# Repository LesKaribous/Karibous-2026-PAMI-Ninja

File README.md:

# Karibous-2026-PAMI-Ninja
PAMI Ninja - Coupe de France de robotique 2026

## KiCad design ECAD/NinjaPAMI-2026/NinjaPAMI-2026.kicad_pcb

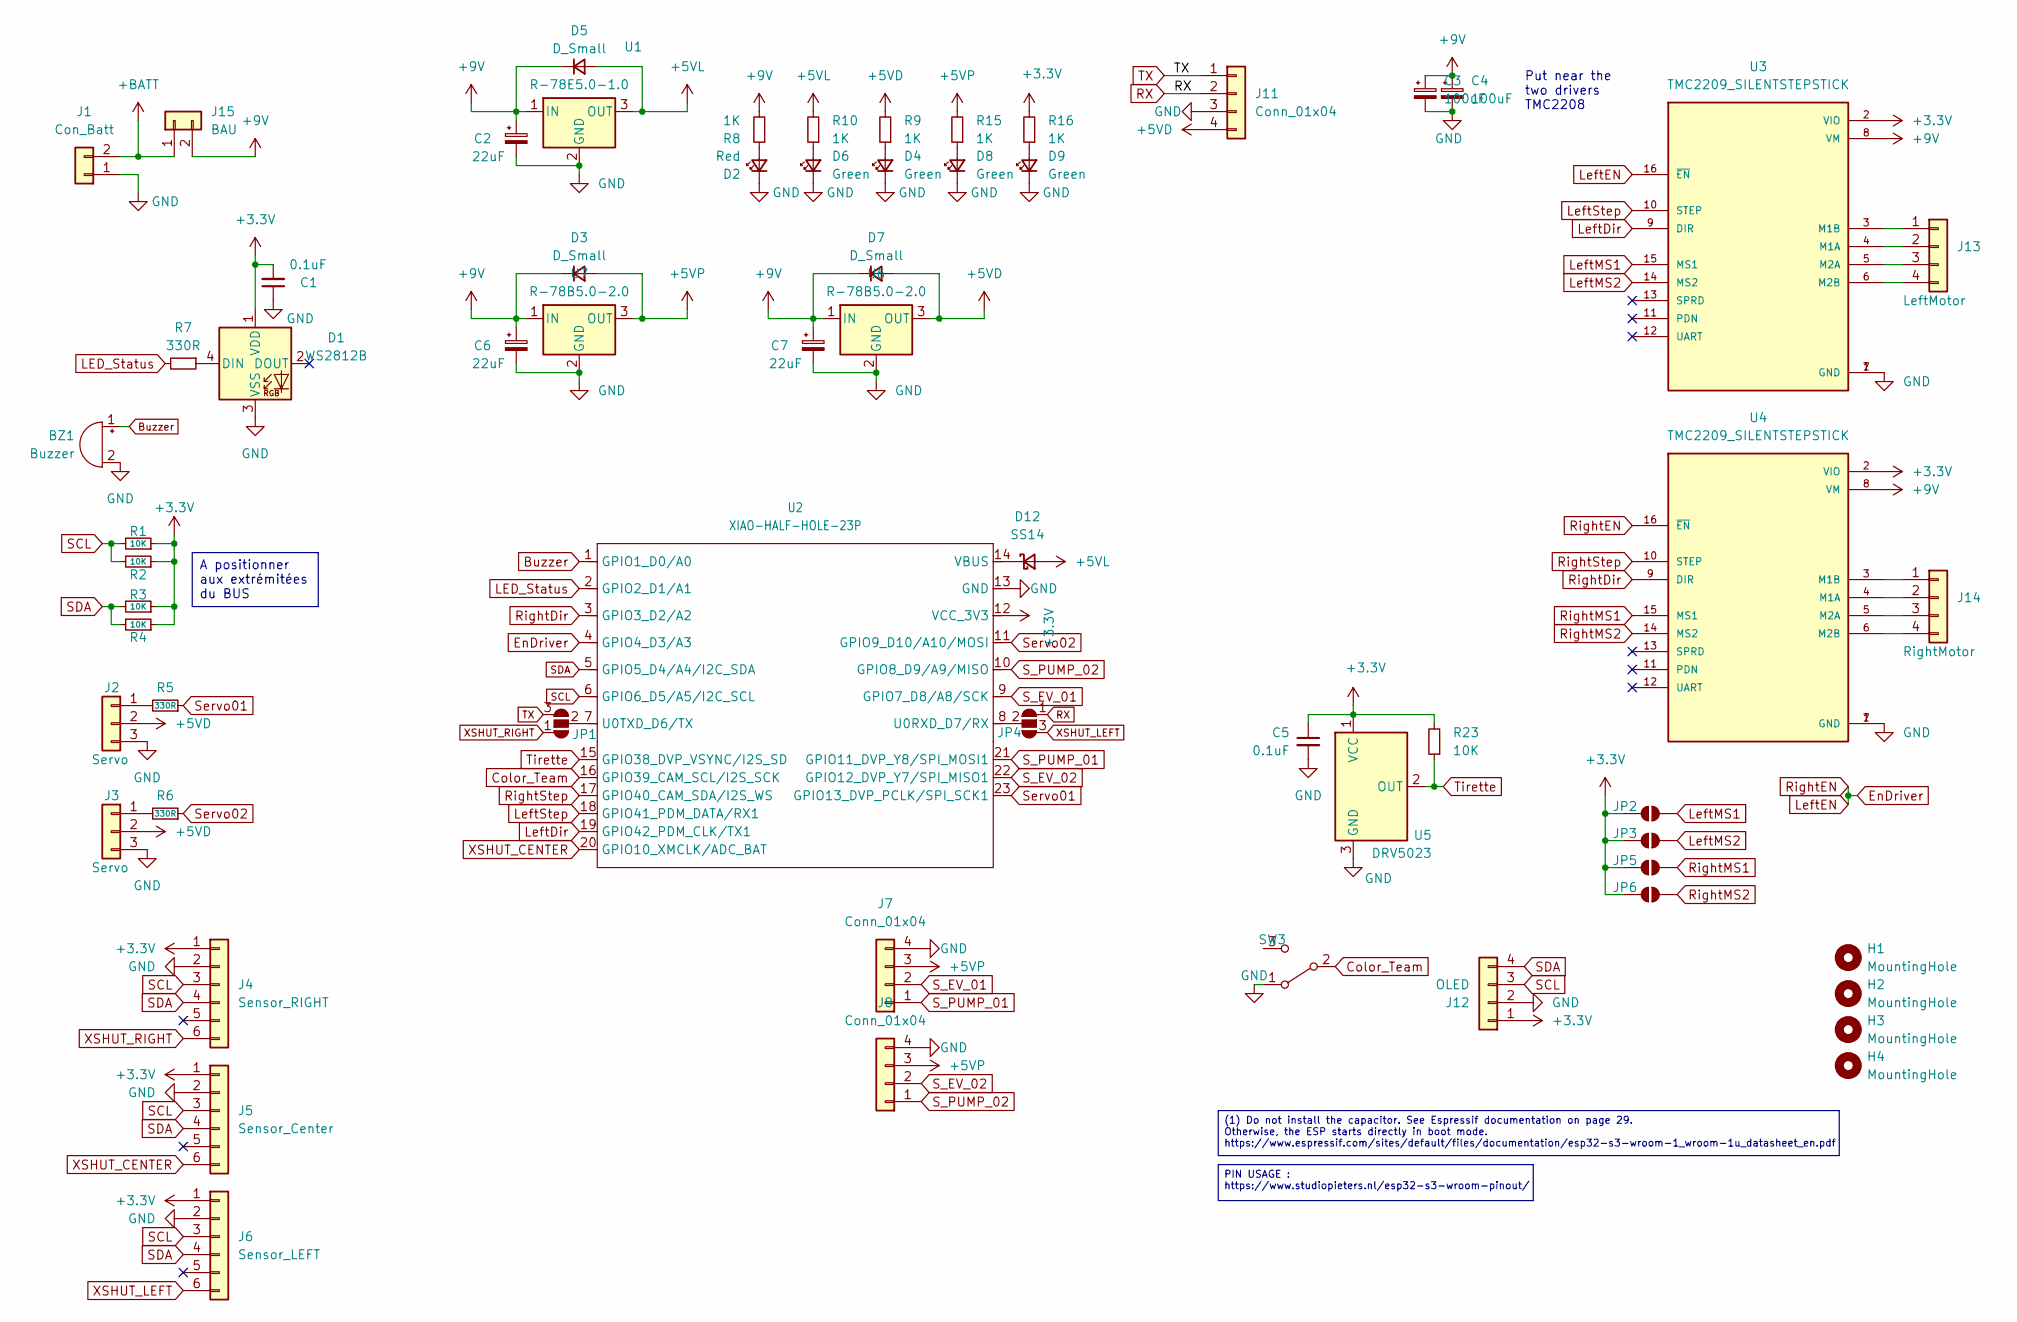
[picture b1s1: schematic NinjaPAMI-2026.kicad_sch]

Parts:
BZ1: Buzzer; Buzzer_12x9.5RM7.6
C1: 0.1uF; C_1206_3216Metric
C2, C6, C7: 22uF; CP_Elec_5x5.4
C3, C4: 100uF; CP_Radial_D8.0mm_P3.50mm
C5: 0.1uF; C_1206_3216Metric_Pad1.33x1.80mm_HandSolder
D1: WS2812B; LED_WS2812B_PLCC4_5.0x5.0mm_P3.2mm
D2: Red; LED_1206_3216Metric
D3, D5, D7: D_Small; D_SMA_Handsoldering
D4, D6, D8, D9: Green; LED_1206_3216Metric
D12: SS14; D_SMA_Handsoldering
H1, H2, H3, H4: MountingHole; MountingHole_3.2mm_M3
J1: Con_Batt; Molex_KK-254_AE-6410-02A_1x02_P2.54mm_Vertical
J2, J3: Servo; PinHeader_1x03_P2.54mm_Vertical
J4: Sensor_RIGHT; Molex_KK-254_AE-6410-06A_1x06_P2.54mm_Vertical
J5: Sensor_Center; Molex_KK-254_AE-6410-06A_1x06_P2.54mm_Vertical
J6: Sensor_LEFT; Molex_KK-254_AE-6410-06A_1x06_P2.54mm_Vertical
J7, J8, J11: Conn_01x04; Molex_KK-254_AE-6410-04A_1x04_P2.54mm_Vertical
J12: OLED; Molex_KK-254_AE-6410-04A_1x04_P2.54mm_Vertical
J13: LeftMotor; Molex_KK-254_AE-6410-04A_1x04_P2.54mm_Vertical
J14: RightMotor; Molex_KK-254_AE-6410-04A_1x04_P2.54mm_Vertical
J15: BAU; Molex_KK-254_AE-6410-02A_1x02_P2.54mm_Vertical
JP1, JP4: SolderJumper_3_Open; SolderJumper-3_P1.3mm_Open_RoundedPad1.0x1.5mm_NumberLabels
JP2, JP3, JP5, JP6: SolderJumper_2_Open; SolderJumper-2_P1.3mm_Open_RoundedPad1.0x1.5mm
R1, R2, R3, R4, R23: 10K; R_1206_3216Metric_Pad1.30x1.75mm_HandSolder
R5, R6, R7: 330R; R_1206_3216Metric_Pad1.30x1.75mm_HandSolder
R8, R9, R10, R15, R16: 1K; R_1206_3216Metric_Pad1.30x1.75mm_HandSolder
SW3: SW_SPDT; SK-12D10 1P2T
U1: R-78E5.0-1.0; Converter_DCDC_RECOM_R-78E-0.5_THT
U2: XIAO-HALF-HOLE-23P; MOUDLE23P-SMD-2.54-21X17.8MM.kicad_mod.kicad_sym
U3, U4: TMC2209_SILENTSTEPSTICK; MODULE_TMC2209_SILENTSTEPSTICK; PARTREV 1.20
U5: DRV5023; SOT-23_Handsoldering
U6, U7: R-78B5.0-2.0; Converter_DCDC_RECOM_R-78B-2.0_THT

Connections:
+3.3V: C1.2, C5.1, D1.1 (VDD), J4.1, J5.1, J6.1, J12.1, JP2.1 (A), JP3.1 (A), JP5.1 (A), JP6.1 (A), R1.1, R2.1, R3.1, R4.1, R16.2, R23.2, U2.12 (VCC_3V3), U3.2 (VIO), U4.2 (VIO), U5.1 (VCC)
+5VD: D7.2 (A), J2.2, J3.2, J11.4, R9.2, U6.3 (OUT)
+5VL: D5.2 (A), D12.2 (A), R10.2, U1.3 (OUT)
+5VP: D3.2 (A), J7.3, J8.3, R15.2, U7.3 (OUT)
+9V: C2.1, C3.1, C4.1, C6.1, C7.1, D3.1 (K), D5.1 (K), D7.1 (K), J15.2, R8.2, U1.1 (IN), U3.8 (VM), U4.8 (VM), U6.1 (IN), U7.1 (IN)
+BATT: J1.2, J15.1
Buzzer: BZ1.1 (+), U2.1 (GPIO1_D0/A0)
Color_Team: SW3.2 (B), U2.16 (GPIO39_CAM_SCL/I2S_SCK)
EnDriver: U2.4 (GPIO4_D3/A3), U3.16 (~EN), U4.16 (~EN)
GND: BZ1.2 (-), C1.1, C2.2, C3.2, C4.2, C5.2, C6.2, C7.2, D1.3 (VSS), D2.1 (K), D4.1 (K), D6.1 (K), D8.1 (K), D9.1 (K), J1.1, J2.3, J3.3, J4.2, J5.2, J6.2, J7.4, J8.4, J11.3, J12.2, SW3.1 (A), U1.2 (GND), U2.13 (GND), U3.1 (GND), U3.7 (GND), U4.1 (GND), U4.7 (GND), U5.3 (GND), U6.2 (GND), U7.2 (GND)
LED_Status: R7.2, U2.2 (GPIO2_D1/A1)
LeftDir: U2.19 (GPIO42_PDM_CLK/TX1), U3.9 (DIR)
LeftMS1: JP2.2 (B), U3.15 (MS1)
LeftMS2: JP3.2 (B), U3.14 (MS2)
LeftStep: U2.18 (GPIO41_PDM_DATA/RX1), U3.10 (STEP)
unnamed: D1.4 (DIN), R7.1
unnamed: D2.2 (A), R8.1
unnamed: D4.2 (A), R9.1
unnamed: D6.2 (A), R10.1
unnamed: D8.2 (A), R15.1
unnamed: D9.2 (A), R16.1
unnamed: D12.1 (K), U2.14 (VBUS)
unnamed: J2.1, R5.2
unnamed: J3.1, R6.2
unnamed: J13.1, U3.3 (M1B)
unnamed: J13.2, U3.4 (M1A)
unnamed: J13.3, U3.5 (M2A)
unnamed: J13.4, U3.6 (M2B)
unnamed: J14.1, U4.3 (M1B)
unnamed: J14.2, U4.4 (M1A)
unnamed: J14.3, U4.5 (M2A)
unnamed: J14.4, U4.6 (M2B)
unnamed: JP1.2 (C), U2.7 (U0TXD_D6/TX)
unnamed: JP4.2 (C), U2.8 (U0RXD_D7/RX)
RX: J11.2, JP4.1 (A)
RightDir: U2.3 (GPIO3_D2/A2), U4.9 (DIR)
RightMS1: JP5.2 (B), U4.15 (MS1)
RightMS2: JP6.2 (B), U4.14 (MS2)
RightStep: U2.17 (GPIO40_CAM_SDA/I2S_WS), U4.10 (STEP)
SCL: J4.3, J5.3, J6.3, J12.3, R1.2, R2.2, U2.6 (GPIO6_D5/A5/I2C_SCL)
SDA: J4.4, J5.4, J6.4, J12.4, R3.2, R4.2, U2.5 (GPIO5_D4/A4/I2C_SDA)
S_EV_01: J7.2, U2.9 (GPIO7_D8/A8/SCK)
S_EV_02: J8.2, U2.22 (GPIO12_DVP_Y7/SPI_MISO1)
S_PUMP_01: J7.1, U2.21 (GPIO11_DVP_Y8/SPI_MOSI1)
S_PUMP_02: J8.1, U2.10 (GPIO8_D9/A9/MISO)
Servo01: R5.1, U2.23 (GPIO13_DVP_PCLK/SPI_SCK1)
Servo02: R6.1, U2.11 (GPIO9_D10/A10/MOSI)
TX: J11.1, JP1.3 (B)
Tirette: R23.1, U2.15 (GPIO38_DVP_VSYNC/I2S_SD), U5.2 (OUT)
XSHUT_CENTER: J5.6, U2.20 (GPIO10_XMCLK/ADC_BAT)
XSHUT_LEFT: J6.6, JP4.3 (B)
XSHUT_RIGHT: J4.6, JP1.1 (A)

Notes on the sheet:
Put near the two drivers TMC2208
PIN USAGE : https://www.studiopieters.nl/esp32-s3-wroom-pinout/
A positionner aux extrémitées du BUS
(1) Do not install the capacitor. See Espressif documentation on page 29. Otherwise, the ESP starts directly in boot mode. https://www.espressif.com/sites/default/files/documentation/esp32-s3-wroom-1_wroom-1u_datasheet_en.pdf

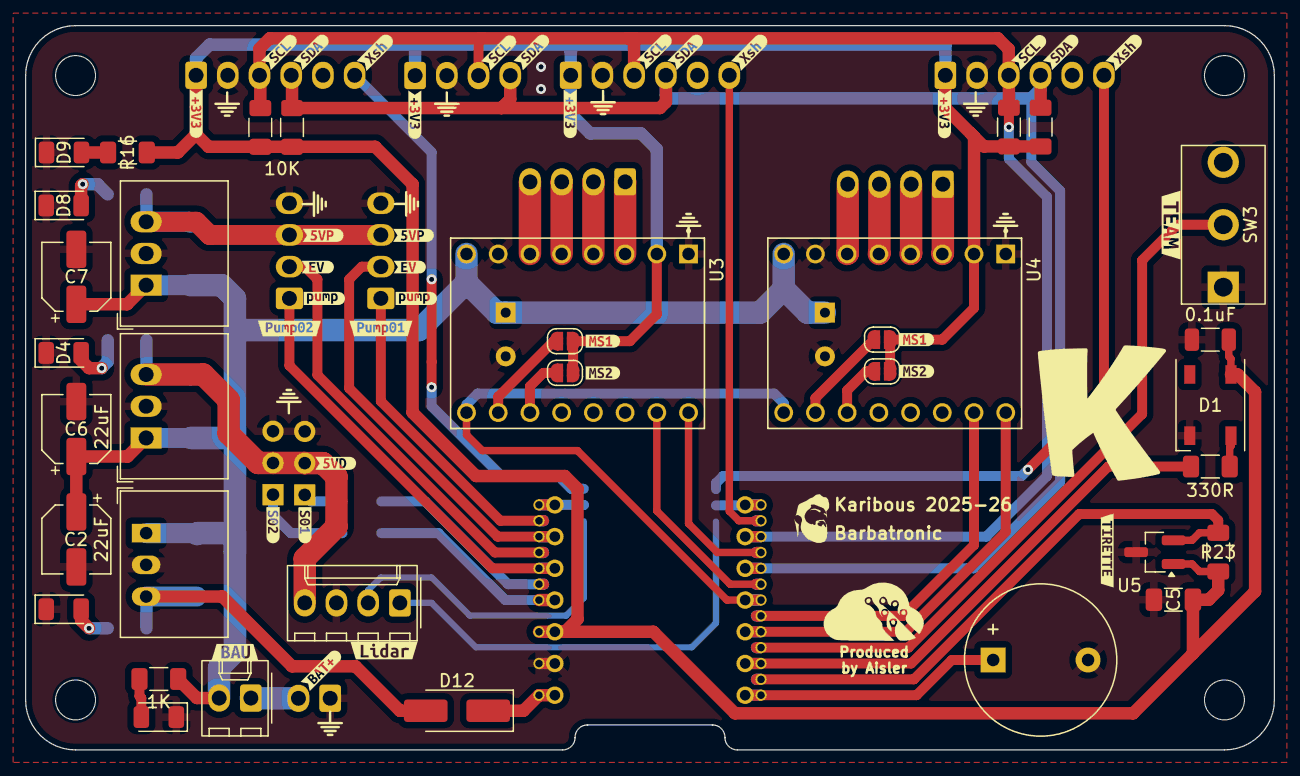
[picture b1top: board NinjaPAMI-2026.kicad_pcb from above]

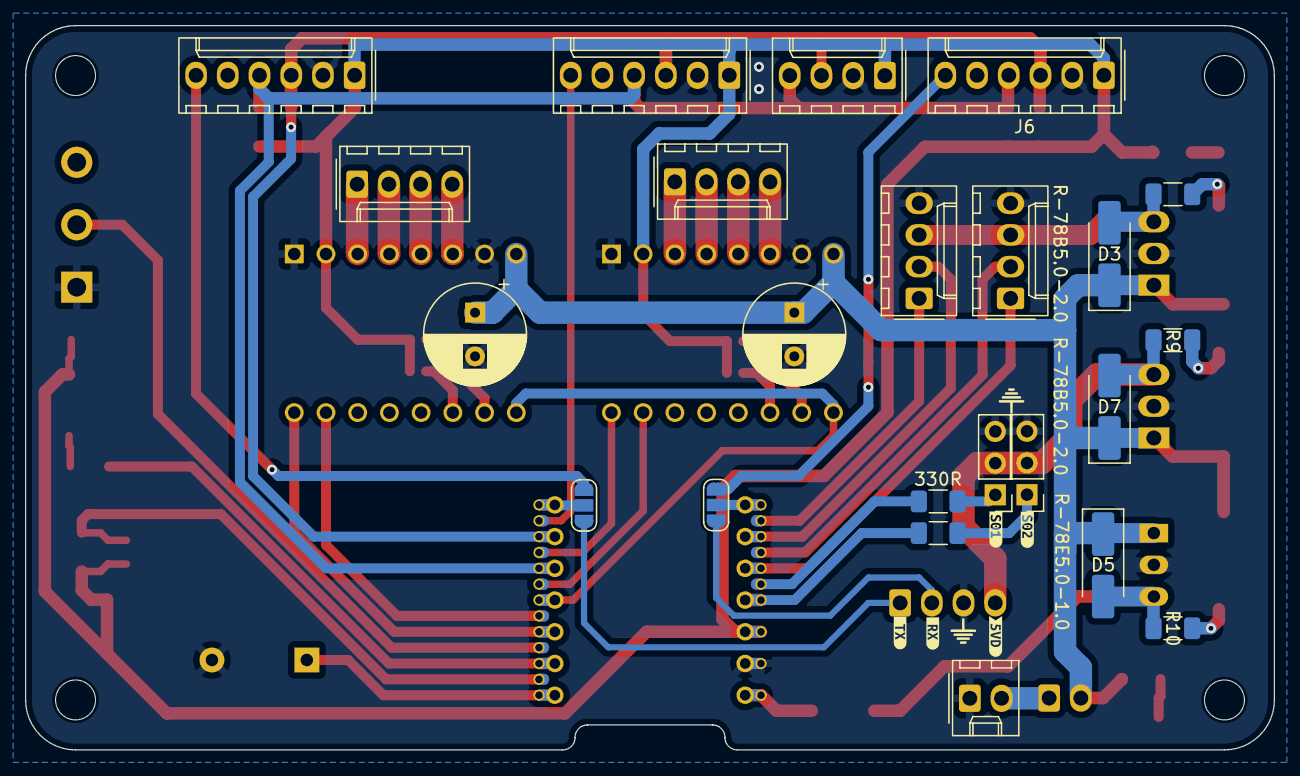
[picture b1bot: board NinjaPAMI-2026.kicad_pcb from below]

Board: 2 copper layers, 100.0 x 58.0 mm, 102 parts (28 on the bottom side), 52 nets.

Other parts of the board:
kibuzzard-670C04A5, kibuzzard-670C04A5#2, kibuzzard-670C04A5#3, kibuzzard-670C04A5#4: G***; kibuzzard-670C04A5
kibuzzard-670C07A3: G***; kibuzzard-670C07A3
kibuzzard-670C23C9: G***; kibuzzard-670C23C9
kibuzzard-670C047F: G***; kibuzzard-670C047F
kibuzzard-670C0507: G***; kibuzzard-670C0507
kibuzzard-670C0798: G***; kibuzzard-670C0798
kibuzzard-6998F5BE: G***; kibuzzard-6998F5BE
kibuzzard-6998F5D7: G***; kibuzzard-6998F5D7
kibuzzard-6998F8A6, kibuzzard-6998F8A6#2: G***; kibuzzard-6998F8A6
kibuzzard-6998F8DE: G***; kibuzzard-6998F8DE
kibuzzard-6998F8EA: G***; kibuzzard-6998F8EA
kibuzzard-6998F9AD, kibuzzard-6998F9AD#2: G***; kibuzzard-6998F9AD
kibuzzard-6998F92F, kibuzzard-6998F92F#2: G***; kibuzzard-6998F92F
kibuzzard-6998F94E, kibuzzard-6998F94E#2: G***; kibuzzard-6998F94E
kibuzzard-6998F900, kibuzzard-6998F900#2: G***; kibuzzard-6998F900
kibuzzard-6998F954, kibuzzard-6998F954#2: G***; kibuzzard-6998F954
kibuzzard-6998FA9D, kibuzzard-6998FA9D#2, kibuzzard-6998FA9D#3, kibuzzard-6998FA9D#4: G***; kibuzzard-6998FA9D
kibuzzard-6998FAED, kibuzzard-6998FAED#2, kibuzzard-6998FAED#3, kibuzzard-6998FAED#4: G***; kibuzzard-6998FAED
kibuzzard-6998FB46, kibuzzard-6998FB46#2, kibuzzard-6998FB46#3: G***; kibuzzard-6998FB46
kibuzzard-6998FE5D, kibuzzard-6998FE5D#2: G***; kibuzzard-6998FE5D
kibuzzard-6998FE66, kibuzzard-6998FE66#2: G***; kibuzzard-6998FE66

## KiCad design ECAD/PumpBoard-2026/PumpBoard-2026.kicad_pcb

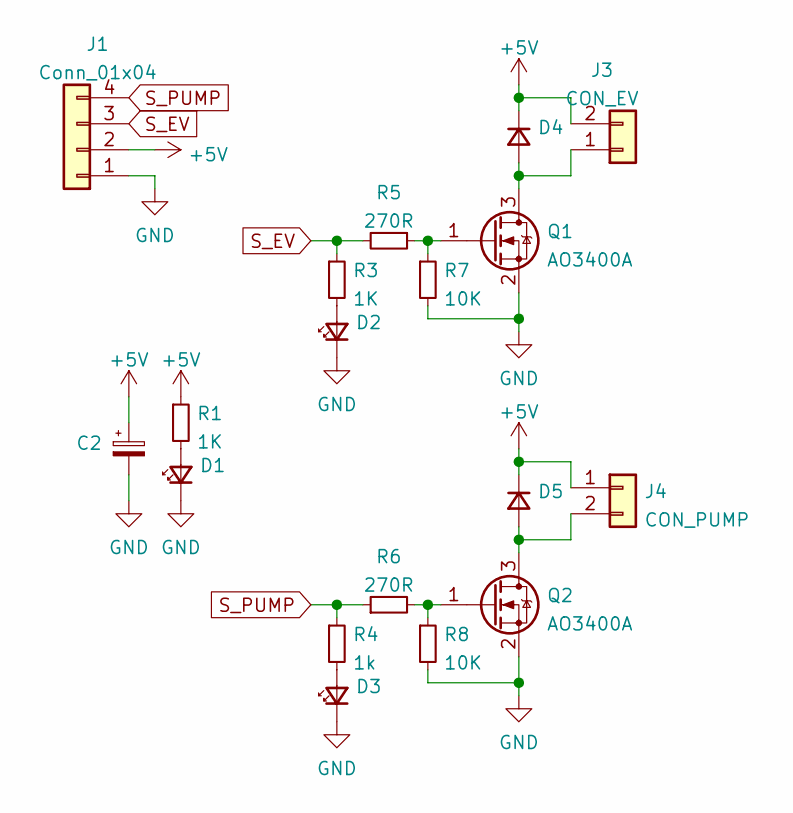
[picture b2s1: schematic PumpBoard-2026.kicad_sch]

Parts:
C2: C_Polarized_Small; CP_Radial_D8.0mm_P5.00mm
D1, D2, D3: LED_Small; LED_1206_3216Metric_Pad1.42x1.75mm_HandSolder
D4, D5: D_Small; D_SMA_Handsoldering
J1: Conn_01x04; PinHeader_1x04_P2.54mm_Vertical
J3: CON_EV; Molex_KK-254_AE-6410-02A_1x02_P2.54mm_Vertical
J4: CON_PUMP; motor-pump-370
Q1, Q2: AO3400A; SOT-23
R1, R3: 1K; R_1206_3216Metric_Pad1.30x1.75mm_HandSolder
R4: 1k; R_1206_3216Metric_Pad1.30x1.75mm_HandSolder
R5, R6: 270R; R_1206_3216Metric_Pad1.30x1.75mm_HandSolder
R7, R8: 10K; R_1206_3216Metric_Pad1.30x1.75mm_HandSolder

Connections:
+5V: C2.1, D4.1 (K), D5.1 (K), J1.2, J3.2, J4.1, R1.1
GND: C2.2, D1.1 (K), D2.1 (K), D3.1 (K), J1.1, Q1.2 (S), Q2.2 (S), R7.2, R8.2
unnamed: D1.2 (A), R1.2
unnamed: D2.2 (A), R3.2
unnamed: D3.2 (A), R4.2
unnamed: D4.2 (A), J3.1, Q1.3 (D)
unnamed: D5.2 (A), J4.2, Q2.3 (D)
unnamed: Q1.1 (G), R5.1, R7.1
unnamed: Q2.1 (G), R6.2, R8.1
S_EV: J1.3, R3.1, R5.2
S_PUMP: J1.4, R4.1, R6.1

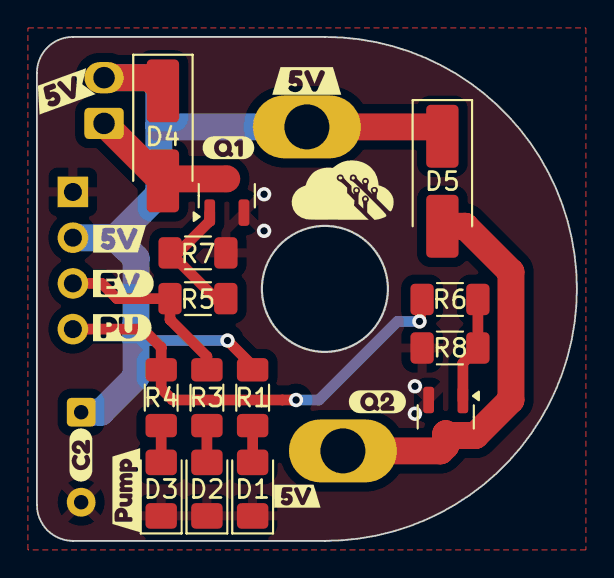
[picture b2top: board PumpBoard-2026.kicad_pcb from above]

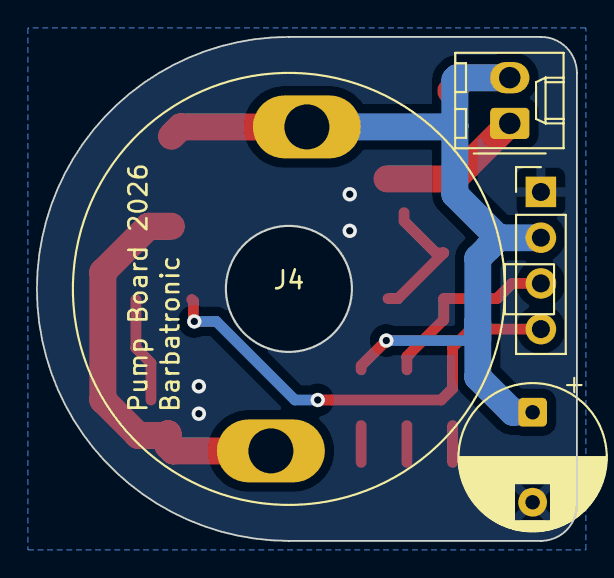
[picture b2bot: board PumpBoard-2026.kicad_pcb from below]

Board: 2 copper layers, 30.0 x 28.0 mm, 28 parts (4 on the bottom side), 11 nets.

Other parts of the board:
kibuzzard-697692E7: G***; kibuzzard-697692E7
kibuzzard-697693AB: G***; kibuzzard-697693AB
kibuzzard-697693BC: G***; kibuzzard-697693BC
kibuzzard-6976928C: G***; kibuzzard-6976928C
kibuzzard-6976930F: G***; kibuzzard-6976930F
kibuzzard-6976945E: G***; kibuzzard-6976945E
kibuzzard-6976947C: G***; kibuzzard-6976947C
kibuzzard-69769280: G***; kibuzzard-69769280
kibuzzard-69769299: G***; kibuzzard-69769299
kibuzzard-69769485: G***; kibuzzard-69769485

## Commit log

2026-01-25 Transfer files from old repo
2026-01-25 placement pump and ev
2026-01-25 routage carte pompe
2026-01-25 modify ARU
2026-01-25 add hall effect sensor
2026-02-20 size refactor - add 2.0 regulator
2026-02-20 ready to order
2026-02-21 routing and silkscreen
2026-03-05 Create .kicad-push
2026-03-20 ninja arm
2026-03-20 fix driver inverted issue
2026-03-20 adapt firmware PAMI 2025 to Ninja 2026
2026-03-22 portage lib adafruit
2026-03-22 portage lib adafruit oled screen
2026-04-04 add roboEyes
2026-04-04 adapt to new meca
2026-04-08 invert eyes
2026-04-08 invert actuators
2026-04-08 trim actuators
2026-04-08 trim motion and motors
2026-04-08 datum Yellow
2026-04-08 fix angle issue
2026-04-08 first strategy
2026-04-09 clean comments
2026-04-09 strategy updated
2026-04-09 add eyes movement at the end
2026-04-09 change debug value
2026-04-09 Add third sensor to check
2026-04-09 change read time
2026-04-09 normalized angle only when asked
2026-04-09 new: multitasking sensor reading
2026-04-09 feat: opponent direction and filtering
2026-04-09 basic strategy
2026-04-17 enhanced strategy
2026-04-17 add relative displacement
2026-04-19 Belgium 2026
2026-05-08 Modified strategy
2026-05-10 fixed blue strategy
2026-05-11 Added orient() and wait() and tweaked strategy
2026-05-11 Added OTA Upload capabilities
2026-05-11 new strategy start by vide grenier
2026-05-13 Ported strat to yellow
2026-05-13 Updated vide grenier strategy
2026-05-14 Added clearance and init datum to strat
2026-05-14 Added intermediary recalage bordure in straight line (merci nesnes)
